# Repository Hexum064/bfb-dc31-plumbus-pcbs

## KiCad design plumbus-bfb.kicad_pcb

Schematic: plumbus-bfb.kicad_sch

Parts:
B1: mode; SW_PTS636_SM43J_SMTR_LFS
B2: key1; DTSM-21R-V-B
B3: key2; DTSM-21R-V-B
B4: key3; DTSM-21R-V-B
B5: key4; DTSM-21R-V-B
B6: reset; SW_PTS636_SM43J_SMTR_LFS
BT1: Battery; BatteryHolder_MPD_BC2AAPC_2xAA
C1, C2: 10uF; C_0603_1608Metric
C3, C6, C7, C8, C9, C11, C15, C16, C17, C18, C19, C20, C21, C22, C23, C24, C25, C26, C27, C28, C29, C30: .1uF; C_0603_1608Metric
C4: 0.1uF; C_0603_1608Metric
C5: 470uF; CP_EIA-7343-31_Kemet-D
C10: 100uF; CP_EIA-3528-12_Kemet-T
C12, C14: .474uF; C_0603_1608Metric
C13: .220uF; C_0603_1608Metric
D1, D2, D3: red; LED_0603_1608Metric
J1: Conn_01x04_Socket; PinHeader_1x04_P2.54mm_Horizontal
J2, J3: Conn_02x03_Odd_Even; PinSocket_2x03_P2.54mm_Vertical
L1: 2.2uH; L_1008_2520Metric
Q1: 2N7002; SOT-23
Q2: PZT2222A/MMBT2222A; SOT-23
R1, R12: 100; R_0603_1608Metric
R2, R6: 10k; R_0603_1608Metric
R3, R4, R5, R8, R9: 1k; R_0603_1608Metric
R7: 22k; R_0603_1608Metric
R10: 510; R_0603_1608Metric
R11: 47; R_0603_1608Metric
R13, R14: 4.7k; R_0603_1608Metric
RV1: 20k; TRIM_3352T-1-103LF
S1: SM150508-7
SW1: SW_SPST; MSS3VTR
U1: ATxmega16E5-M; QFN-32-1EP_5x5mm_P0.5mm_EP3.1x3.1mm
U2: TCA6416APWR; TSSOP-24_4.4x7.8mm_P0.65mm
U3: NCS2211DR2G/SC8002B; SOIC-8_3.9x4.9mm_P1.27mm
U4: TPS63001DRCR; VREG_V62_16624-01YE
U5, U6, U7, U8, U9, U10, U11, U12, U13, U14, U15, U16, U17, U18, U19, U20: KTH1601SL-ST3; SOT-23-3
U21, U22, U23, U24, U25, U26, U27, U28, U29, U30, U31, U32, U33, U34, U35, U36, U37, U38, U39, U40, U41, U42, U43, U44, U45, U46, U47, U48, U49, U50, U51, U52, U53, U54, U55, U56, U57, U58, U59, U60, U61, U62, U63, U64, U65, U66, U67, U68, U69, U70, U71, U72, U73, U74, U75, U76: ws2812b-1010

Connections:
+3.3V: C2.1, C3.1, C5.1, C6.1, C7.1, C8.1, C9.1, C10.1, C15.1, C16.1, C17.1, C18.1, C19.1, C20.1, C21.1, C22.1, C23.1, C24.1, C25.1, C26.1, C27.1, C28.1, C29.1, C30.1, J1.4, J2.1, J3.1, R2.1, R13.2, R14.1, U1.17 (VCC), U1.32 (AVCC), U2.2 (VCC1), U2.24 (VCCP), U3.6 (VCC), U4.1 (VOUT), U4.10 (FB), U5.1 (VCC), U6.1 (VCC), U7.1 (VCC), U8.1 (VCC), U9.1 (VCC), U10.1 (VCC), U11.1 (VCC), U12.1 (VCC), U13.1 (VCC), U14.1 (VCC), U15.1 (VCC), U16.1 (VCC), U17.1 (VCC), U18.1 (VCC), U19.1 (VCC), U20.1 (VCC), U21.2 (VDD), U22.2 (VDD), U23.2 (VDD), U24.2 (VDD), U25.2 (VDD), U26.2 (VDD), U27.2 (VDD), U28.2 (VDD), U29.2 (VDD), U30.2 (VDD), U31.2 (VDD), U32.2 (VDD), U33.2 (VDD), U34.2 (VDD), U35.2 (VDD), U36.2 (VDD), U37.2 (VDD), U38.2 (VDD), U39.2 (VDD), U40.2 (VDD), U41.2 (VDD), U42.2 (VDD), U43.2 (VDD), U44.2 (VDD), U45.2 (VDD), U46.2 (VDD), U47.2 (VDD), U48.2 (VDD), U49.2 (VDD), U50.2 (VDD), U51.2 (VDD), U52.2 (VDD), U53.2 (VDD), U54.2 (VDD), U55.2 (VDD), U56.2 (VDD), U57.2 (VDD), U58.2 (VDD), U59.2 (VDD), U60.2 (VDD), U61.2 (VDD), U62.2 (VDD), U63.2 (VDD), U64.2 (VDD), U65.2 (VDD), U66.2 (VDD), U67.2 (VDD), U68.2 (VDD), U69.2 (VDD), U70.2 (VDD), U71.2 (VDD), U72.2 (VDD), U73.2 (VDD), U74.2 (VDD), U75.2 (VDD), U76.2 (VDD)
GND: B1.2, B6.1, BT1.2 (-), C1.2, C2.2, C3.2, C4.2, C5.2, C7.2, C9.2, C10.2, C11.2, C13.2, J1.1, J2.2, J3.2, Q1.2 (S), R3.1, R4.1, R5.1, R6.1, U1.1 (GND), U1.18 (GND), U1.33 (GND), U3.1 (ENABLE), U3.7 (VEE), U4.3 (PGND), U4.9 (GND), U4.11 (THERMAL_PAD), U21.3 (GND), U22.3 (GND), U23.3 (GND), U24.3 (GND), U25.3 (GND), U26.3 (GND), U27.3 (GND), U28.3 (GND), U29.3 (GND), U30.3 (GND), U31.3 (GND), U32.3 (GND), U33.3 (GND), U34.3 (GND), U35.3 (GND), U36.3 (GND), U37.3 (GND), U38.3 (GND), U39.3 (GND), U40.3 (GND), U41.3 (GND), U42.3 (GND), U43.3 (GND), U44.3 (GND), U45.3 (GND), U46.3 (GND), U47.3 (GND), U48.3 (GND), U49.3 (GND), U50.3 (GND), U51.3 (GND), U52.3 (GND), U53.3 (GND), U54.3 (GND), U55.3 (GND), U56.3 (GND), U57.3 (GND), U58.3 (GND), U59.3 (GND), U60.3 (GND), U61.3 (GND), U62.3 (GND), U63.3 (GND), U64.3 (GND), U65.3 (GND), U66.3 (GND), U67.3 (GND), U68.3 (GND), U69.3 (GND), U70.3 (GND), U71.3 (GND), U72.3 (GND), U73.3 (GND), U74.3 (GND), U75.3 (GND), U76.3 (GND); also elsewhere on the board
unnamed: C12.1, R11.1, R12.1
unnamed: C12.2, R7.2
unnamed: C13.1, C14.2, R8.2
unnamed: C14.1, R9.1
unnamed: D1.2 (A), U1.23 (PD5)
unnamed: D1.1 (K), R5.2
unnamed: D2.2 (A), U1.22 (PD6)
unnamed: D2.1 (K), R4.2
unnamed: D3.2 (A), U1.21 (PD7)
unnamed: D3.1 (K), R3.2
unnamed: J1.2, U1.7 (PDI_DATA)
unnamed: B6.2, J1.3, U1.8 (~RESET/PDI_CLK)
unnamed: J2.5, J3.5, R9.2
unnamed: J2.6, U1.10 (PC6)
unnamed: J3.6, U1.11 (PC5)
unnamed: Q1.1 (G), R6.2, U1.9 (PC7)
unnamed: Q2.1 (B), R10.1
unnamed: Q2.2 (C), U1.12 (PC4)
unnamed: Q2.3 (E), R12.2
unnamed: R7.1, R8.1, RV1.1
unnamed: B1.1, U1.6 (AREF/PA0)
unnamed: R10.2, U1.4 (PA2)
unnamed 24: B2.1, B2.2, U1.2 (PA4); also elsewhere on the board
unnamed 25: B3.1, B3.2, U1.31 (PA5); also elsewhere on the board
unnamed 26: B4.1, B4.2, U1.30 (PA6); also elsewhere on the board
unnamed 27: B5.1, B5.2, U1.29 (PA7); also elsewhere on the board
unnamed: U1.28 (PD0/AREF), U21.4 (DI)
unnamed: R11.2, U1.24 (PD4)
unnamed: U2.4 (P00), U5.2 (VOUT)
unnamed: U2.5 (P01), U6.2 (VOUT)
unnamed: U2.6 (P02), U7.2 (VOUT)
unnamed: U2.7 (P03), U8.2 (VOUT)
unnamed: U2.8 (P04), U9.2 (VOUT)
unnamed: U2.20 (P17), U20.2 (VOUT)
unnamed: R2.2, U2.3 (~RESET)
unnamed: C11.1, U3.2 (BIAS), U3.3 (IN+)
unnamed: RV1.2, U3.4 (IN-)
unnamed: RV1.3, S1.1, U3.5 (OUT+)
unnamed: S1.2, U3.8 (OUT-)
unnamed: C4.1, R1.2, U4.6 (EN), U4.7 (PS/SYNC), U4.8 (VINA)
unnamed: L1.2, U4.4 (L1)
unnamed: L1.1, U4.2 (L2)
unnamed: U2.9 (P05), U10.2 (VOUT)
unnamed: U2.10 (P06), U11.2 (VOUT)
unnamed: U2.11 (P07), U12.2 (VOUT)
unnamed: U2.13 (P10), U13.2 (VOUT)
unnamed: U2.14 (P11), U14.2 (VOUT)
unnamed: U2.15 (P12), U15.2 (VOUT)
unnamed: U2.16 (P13), U16.2 (VOUT)
unnamed: U2.17 (P14), U17.2 (VOUT)
unnamed: U2.18 (P15), U18.2 (VOUT)
unnamed: U2.19 (P16), U19.2 (VOUT)
unnamed: U21.1 (DO), U22.4 (DI)
unnamed: U22.1 (DO), U23.4 (DI)
unnamed: U23.1 (DO), U24.4 (DI)
unnamed: U24.1 (DO), U25.4 (DI)
unnamed: U25.1 (DO), U26.4 (DI)
unnamed: U26.1 (DO), U27.4 (DI)
unnamed: U27.1 (DO), U28.4 (DI)
unnamed: U28.1 (DO), U29.4 (DI)
unnamed: U29.1 (DO), U30.4 (DI)
unnamed: U30.1 (DO), U31.4 (DI)
unnamed: U31.1 (DO), U32.4 (DI)
unnamed: U32.1 (DO), U33.4 (DI)
unnamed: U33.1 (DO), U34.4 (DI)
unnamed: U34.1 (DO), U35.4 (DI)
unnamed: U35.1 (DO), U36.4 (DI)
unnamed: U36.1 (DO), U37.4 (DI)
unnamed: U37.1 (DO), U38.4 (DI)
unnamed: U38.1 (DO), U39.4 (DI)
unnamed: U39.1 (DO), U40.4 (DI)
unnamed: U40.1 (DO), U41.4 (DI)
unnamed: U41.1 (DO), U42.4 (DI)
unnamed: U42.1 (DO), U43.4 (DI)
unnamed: U43.1 (DO), U44.4 (DI)
unnamed: U44.1 (DO), U45.4 (DI)
unnamed: U45.1 (DO), U46.4 (DI)
unnamed: U46.1 (DO), U47.4 (DI)
unnamed: U47.1 (DO), U48.4 (DI)
unnamed: U48.1 (DO), U49.4 (DI)
unnamed: U49.1 (DO), U50.4 (DI)
unnamed: U50.1 (DO), U51.4 (DI)
unnamed: U51.1 (DO), U52.4 (DI)
unnamed: U52.1 (DO), U53.4 (DI)
unnamed: U53.1 (DO), U54.4 (DI)
unnamed: U54.1 (DO), U55.4 (DI)
unnamed: U55.1 (DO), U56.4 (DI)
unnamed: U56.1 (DO), U57.4 (DI)
unnamed: U57.1 (DO), U58.4 (DI)
unnamed: U58.1 (DO), U59.4 (DI)
unnamed: U59.1 (DO), U60.4 (DI)
unnamed: U60.1 (DO), U61.4 (DI)
unnamed: U61.1 (DO), U62.4 (DI)
unnamed: U62.1 (DO), U63.4 (DI)
unnamed: U63.1 (DO), U64.4 (DI)
unnamed: U64.1 (DO), U65.4 (DI)
unnamed: U65.1 (DO), U66.4 (DI)
unnamed: U66.1 (DO), U67.4 (DI)
unnamed: U67.1 (DO), U68.4 (DI)
unnamed: U68.1 (DO), U69.4 (DI)
unnamed: U69.1 (DO), U70.4 (DI)
unnamed: U70.1 (DO), U71.4 (DI)
unnamed: U71.1 (DO), U72.4 (DI)
unnamed: U72.1 (DO), U73.4 (DI)
unnamed: U73.1 (DO), U74.4 (DI)
unnamed: U74.1 (DO), U75.4 (DI)
unnamed: U75.1 (DO), U76.4 (DI)
SCL: J2.4, J3.4, R13.1, U1.15 (PC1), U2.22 (SCL)
SDA: J2.3, J3.3, R14.2, U1.16 (PC0), U2.23 (SDA)
VEE: C6.2, C8.2, C15.2, C16.2, C17.2, C18.2, C19.2, C20.2, C21.2, C22.2, C23.2, C24.2, C25.2, C26.2, C27.2, C28.2, C29.2, C30.2, Q1.3 (D), U2.12 (GND), U2.21 (ADDR), U5.3 (GND), U6.3 (GND), U7.3 (GND), U8.3 (GND), U9.3 (GND), U10.3 (GND), U11.3 (GND), U12.3 (GND), U13.3 (GND), U14.3 (GND), U15.3 (GND), U16.3 (GND), U17.3 (GND), U18.3 (GND), U19.3 (GND), U20.3 (GND)

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
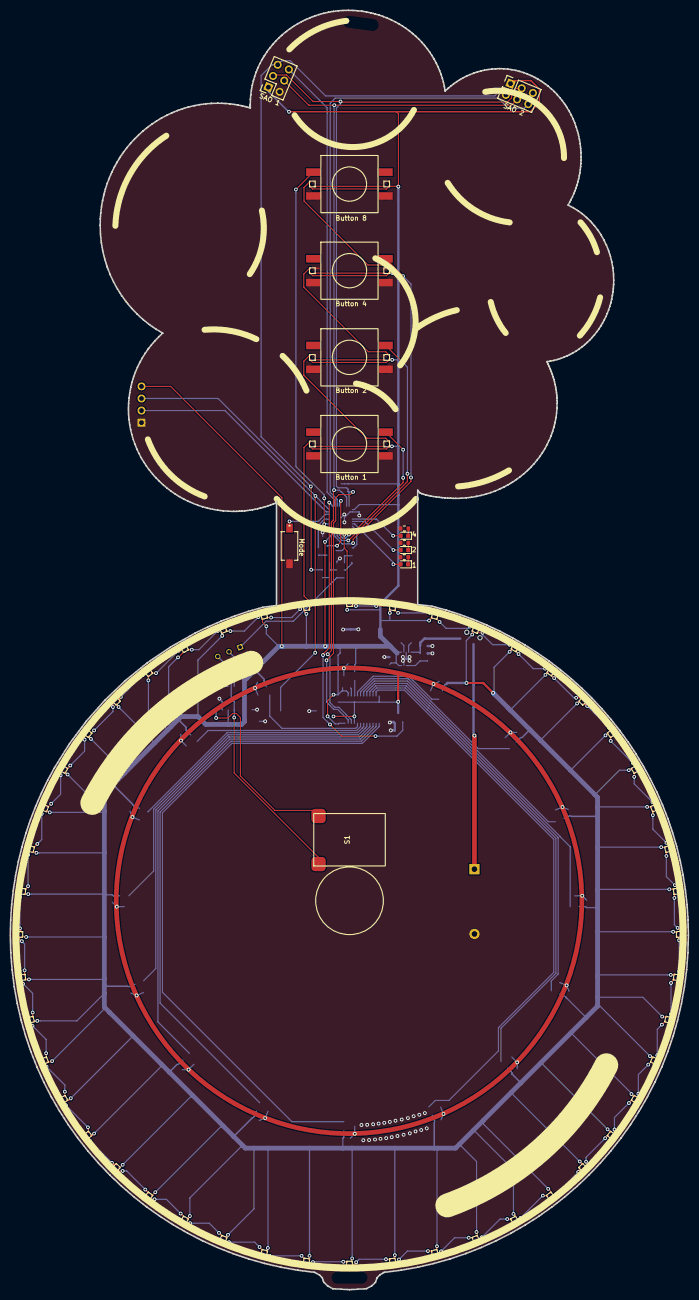
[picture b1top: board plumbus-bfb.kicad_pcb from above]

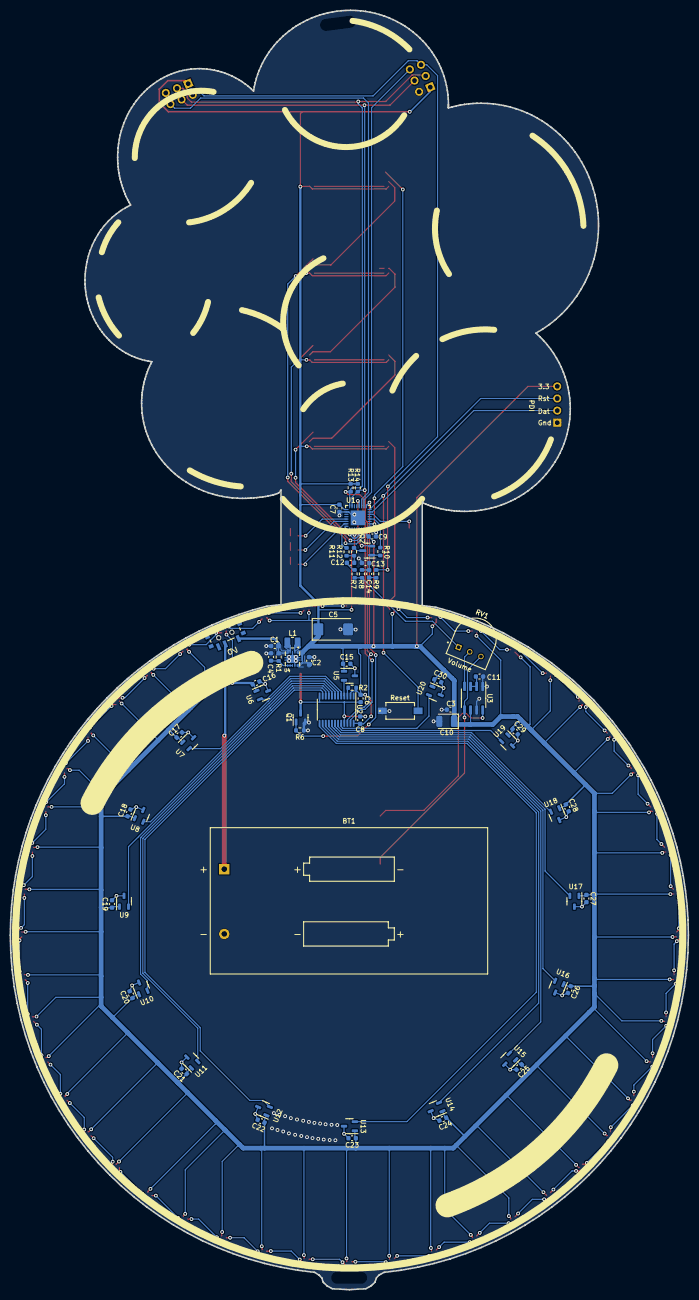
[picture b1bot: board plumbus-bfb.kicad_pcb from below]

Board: 2 copper layers, 142.3 x 268.4 mm, 139 parts (69 on the bottom side), 114 nets.

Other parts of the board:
key1: key1; DTSM-21R-V-B
key2: key2; DTSM-21R-V-B
key3: key3; DTSM-21R-V-B
key4: key4; DTSM-21R-V-B

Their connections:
GND: key1.3 (passive), key1.4 (passive), key2.3 (passive), key2.4 (passive), key3.3 (passive), key3.4 (passive), key4.3 (passive), key4.4 (passive); also elsewhere on the board
unnamed 24: key1.1, key1.2; also elsewhere on the board
unnamed 25: key2.1, key2.2; also elsewhere on the board
unnamed 26: key3.1, key3.2; also elsewhere on the board
unnamed 27: key4.1, key4.2; also elsewhere on the board

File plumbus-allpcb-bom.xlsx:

|  |  | floob-dome-switches BOM
Item # | *Ref Des | *Qty | Manufacturer | *Mfg Part # | Description / Value | *Package | Type | Your Instructions / Notes
1 | B1 | 1 | LCSC | C2800965 | TS-1101-C-W:SW_PTS636_SM43J_SMTR_LFS | TS-1101-C-W:SW_PTS636_SM43J_SMTR_LFS | mode
2 | B6 | 1 | LCSC | C2800965 | TS-1101-C-W:SW_PTS636_SM43J_SMTR_LFS | TS-1101-C-W:SW_PTS636_SM43J_SMTR_LFS | reset
3 | C1, C2 | 2 | LCSC | C19702 | Capacitor_SMD:C_0603_1608Metric | Capacitor_SMD:C_0603_1608Metric | 10uF
4 | C3, C6, C7, C8, C9, C11, C15, C16, C17, C18, C19, C20, C21, C22, C23, C24, C25,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 | 22 | LCSC | C15849 | Capacitor_SMD:C_0603_1608Metric | Capacitor_SMD:C_0603_1608Metric | .1uF
5 | C4 | 1 | LCSC | C14663 | Capacitor_SMD:C_0603_1608Metric | Capacitor_SMD:C_0603_1608Metric | 0.1uF
6 | C5 | 1 | LCSC | C123270 | Capacitor_Tantalum_SMD:CP_EIA-7343-31_Kemet-D | Capacitor_Tantalum_SMD:CP_EIA-7343-31_Kemet-D | 470uF
7 | C10 | 1 | LCSC | C140373 | Capacitor_Tantalum_SMD:CP_EIA-3528-12_Kemet-T | Capacitor_Tantalum_SMD:CP_EIA-3528-12_Kemet-T | 100uF
8 | C12, C14 | 2 | LCSC | C1623 | Capacitor_SMD:C_0603_1608Metric | Capacitor_SMD:C_0603_1608Metric | .474uF
9 | C13 | 1 | LCSC | C5189829 | Capacitor_SMD:C_0603_1608Metric | Capacitor_SMD:C_0603_1608Metric | .220uF
10 | D1, D2, D3 | 3 | LCSC | C965799 | LED_SMD:LED_0603_1608Metric | LED_SMD:LED_0603_1608Metric | red
11 | J2, J3 | 2 | LCSC | C2935983 | Connector_PinSocket_2.54mm:PinSocket_2x03_P2.54mm_Vertical | Connector_PinSocket_2.54mm:PinSocket_2x03_P2.54mm_Vertical | Conn_02x03_Odd_Even
12 | L1 | 1 | LCSC | C488330 | Inductor_SMD:L_1008_2520Metric | Inductor_SMD:L_1008_2520Metric | 2.2uH
13 | Q1 | 1 | LCSC | C8545 | Package_TO_SOT_SMD:SOT-23 | Package_TO_SOT_SMD:SOT-23 | 2N7002
14 | Q2 | 1 | LCSC | C545537 | Package_TO_SOT_SMD:SOT-23 | Package_TO_SOT_SMD:SOT-23 | PZT2222A/MMBT2222A
15 | R1, R12 | 2 | LCSC | C22775 | Resistor_SMD:R_0603_1608Metric | Resistor_SMD:R_0603_1608Metric | 100
16 | R2, R6 | 2 | LCSC | C25804 | Resistor_SMD:R_0603_1608Metric | Resistor_SMD:R_0603_1608Metric | 10k
17 | R3, R4, R5, R8, R9 | 5 | LCSC | C21190 | Resistor_SMD:R_0603_1608Metric | Resistor_SMD:R_0603_1608Metric | 1k
18 | R7 | 1 | LCSC | C31850 | Resistor_SMD:R_0603_1608Metric | Resistor_SMD:R_0603_1608Metric | 22k
19 | R10 | 1 | LCSC | C23193 | Resistor_SMD:R_0603_1608Metric | Resistor_SMD:R_0603_1608Metric | 510
20 | R11 | 1 | LCSC | C23182 | Resistor_SMD:R_0603_1608Metric | Resistor_SMD:R_0603_1608Metric | 47
21 | R13, R14 | 2 | LCSC | C23162 | Resistor_SMD:R_0603_1608Metric | Resistor_SMD:R_0603_1608Metric | 4.7k
22 | SW1 | 1 | LCSC | C730329 | MSS3-V-T/TA-3524A-A1-W:MSS3VTR | MSS3-V-T/TA-3524A-A1-W:MSS3VTR | SW_SPST
24 | U2 | 1 | LCSC | C130203 | Package_SO:TSSOP-24_4.4x7.8mm_P0.65mm | Package_SO:TSSOP-24_4.4x7.8mm_P0.65mm | TCA6416APWR
25 | U3 | 1 | LCSC | C82124 | Package_SO:SOIC-8_3.9x4.9mm_P1.27mm | Package_SO:SOIC-8_3.9x4.9mm_P1.27mm | NCS2211DR2G/SC8002B
26 | U4 | 1 | LCSC | C28060 | TPS63001DRCR:VREG_V62_16624-01YE | TPS63001DRCR:VREG_V62_16624-01YE | TPS63001DRCR
27 | U5, U6, U7, U8, U9, U10, U11, U12, U13, U14, U15, U16, U17, U18, U19, U20 | 16 | LCSC | C516265 | Package_TO_SOT_SMD:SOT-23-3 | Package_TO_SOT_SMD:SOT-23-3 | KTH1601SL-ST3
28 | U21, U22, U23, U24, U25, U26, U27, U28, U29, U30, U31, U32, U33, U34, U35, U36,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 | 56 | LCSC | C5349953 | ws2812b-1010:ws2812b-1010 | ws2812b-1010:ws2812b-1010 | 1mx1m

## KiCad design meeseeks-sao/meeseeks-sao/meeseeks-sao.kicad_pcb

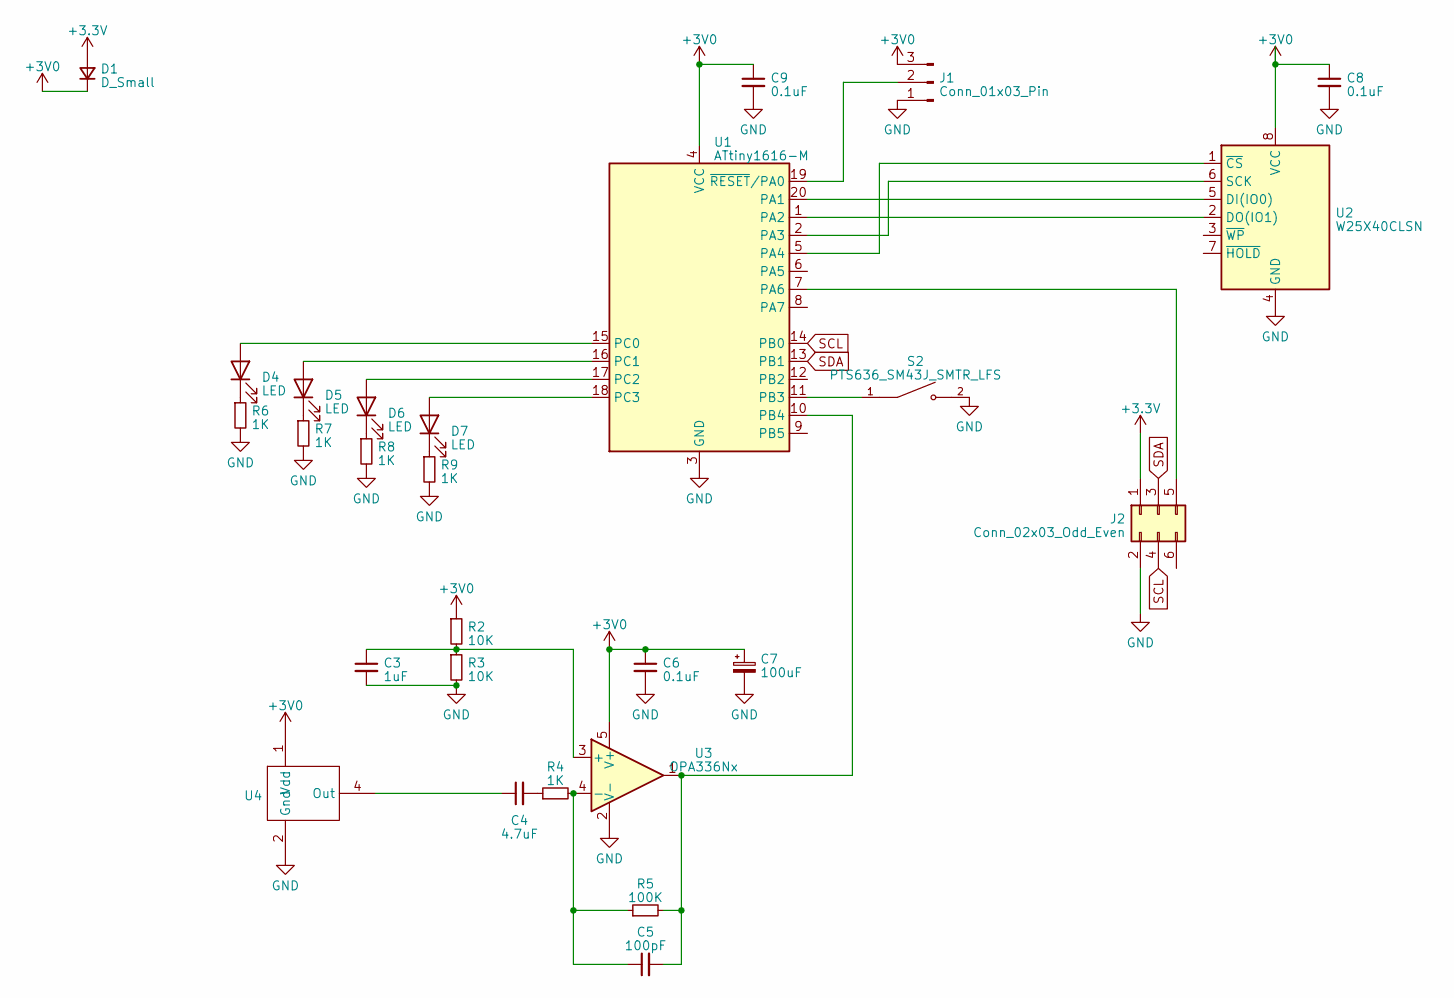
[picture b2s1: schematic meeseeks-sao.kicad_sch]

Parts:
C3: 1uF; C_0603_1608Metric
C4: 4.7uF; C_0603_1608Metric
C5: 100pF; C_0603_1608Metric
C6, C8, C9: 0.1uF; C_0603_1608Metric
C7: 100uF; CP_EIA-3528-12_Kemet-T
D1: D_Small; D_0603_1608Metric
D4, D5, D6, D7: LED; LED_0603_1608Metric
J1: Conn_01x03_Pin; SolderJumper-3_P1.3mm_Open_RoundedPad1.0x1.5mm
J2: Conn_02x03_Odd_Even; PinHeader_2x03_P2.54mm_Vertical
R2, R3: 10K; R_0603_1608Metric
R4, R6, R7, R8, R9: 1K; R_0603_1608Metric
R5: 100K; R_0603_1608Metric
S2: PTS636_SM43J_SMTR_LFS; SW_PTS636_SM43J_SMTR_LFS; PARTREV 27 mar 19
U1: ATtiny1616-M; VQFN-20-1EP_3x3mm_P0.4mm_EP1.7x1.7mm
U2: W25X40CLSN; SOIC-8_3.9x4.9mm_P1.27mm
U3: OPA336Nx; SOT-23-5
U4: NSM2402AT

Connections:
+3.3V: D1.2 (A), J2.1; also elsewhere on the board
+3V0: C6.1, C7.1, C8.1, C9.1, D1.1 (K), J1.3, R2.1, U1.4 (VCC), U2.8 (VCC), U3.5 (V+), U4.1 (Vdd)
GND: C3.2, C6.2, C7.2, C8.2, C9.2, J1.1, J2.2, R3.2, R6.2, R7.2, R8.2, R9.2, S2.2, U1.3 (GND), U1.21 (GND), U2.4 (GND), U3.2 (V-), U4.2 (Gnd), U4.3 (Gnd); also elsewhere on the board
unnamed: C4.2, R4.1
unnamed: D4.2 (A), U1.15 (PC0)
unnamed: D4.1 (K), R6.1
unnamed: D5.2 (A), U1.16 (PC1)
unnamed: D5.1 (K), R7.1
unnamed: D6.2 (A), U1.17 (PC2)
unnamed: D6.1 (K), R8.1
unnamed: D7.2 (A), U1.18 (PC3)
unnamed: D7.1 (K), R9.1
unnamed: J1.2, U1.19 (~RESET/PA0)
unnamed 13: J2.5, U1.7 (PA6); also elsewhere on the board
unnamed: U1.20 (PA1), U2.5 (DI(IO0))
unnamed: U1.1 (PA2), U2.2 (DO(IO1))
unnamed: U1.2 (PA3), U2.6 (SCK)
unnamed: U1.5 (PA4), U2.1 (~CS)
unnamed: S2.1, U1.11 (PB3)
unnamed: C5.2, R5.2, U1.10 (PB4), U3.1
unnamed: C3.1, R2.2, R3.1, U3.3 (+)
unnamed: C5.1, R4.2, R5.1, U3.4 (-)
unnamed: C4.1, U4.4 (Out)
SCL: J2.4, U1.14 (PB0); also elsewhere on the board
SDA: J2.3, U1.13 (PB1); also elsewhere on the board

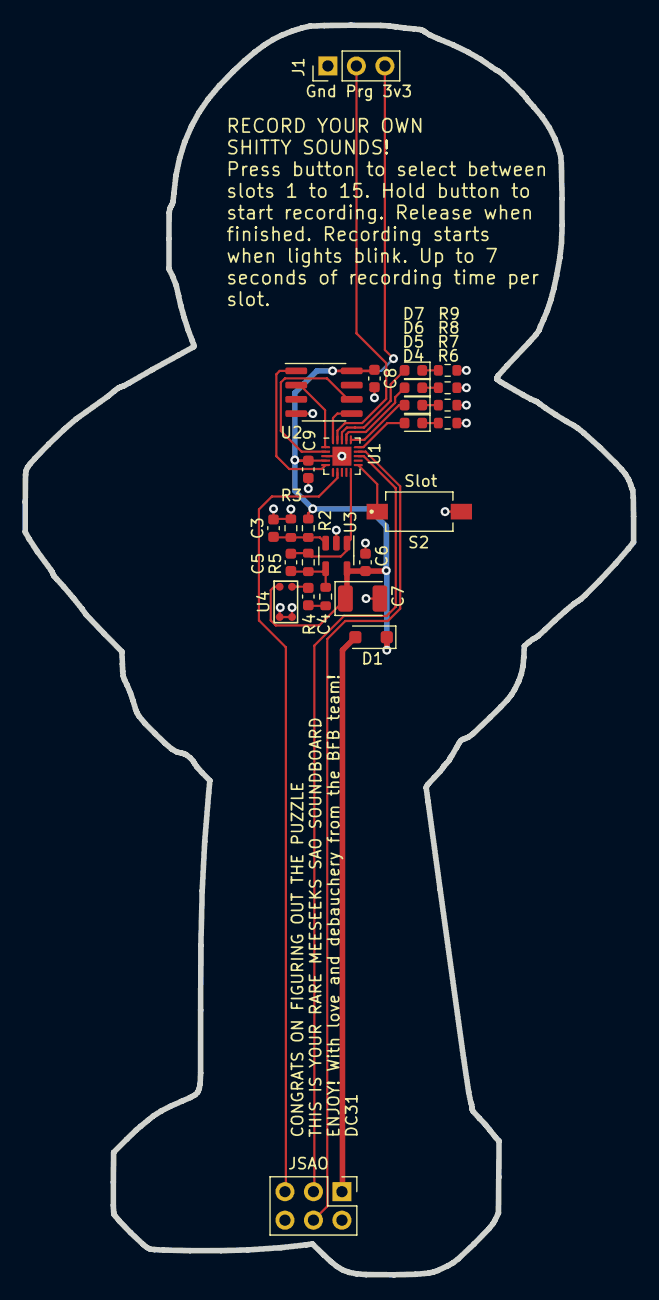
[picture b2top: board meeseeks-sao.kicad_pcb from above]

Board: 2 copper layers, 54.3 x 111.4 mm, 27 parts (0 on the bottom side), 25 nets.

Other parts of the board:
JSAO: Conn_02x03_Odd_Even; PinHeader_2x03_P2.54mm_Vertical

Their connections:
+3.3V: JSAO.1; also elsewhere on the board
GND: JSAO.2; also elsewhere on the board
unnamed 13: JSAO.5; also elsewhere on the board
SCL: JSAO.4; also elsewhere on the board
SDA: JSAO.3; also elsewhere on the board

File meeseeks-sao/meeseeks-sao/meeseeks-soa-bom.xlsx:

Comment | Reference(s) | Footprint | JLCPCB Part #（optional）
1uF | C3 | Capacitor_SMD:C_0603_1608Metric
4.7uF | C4 | Capacitor_SMD:C_0603_1608Metric
100pF | C5 | Capacitor_SMD:C_0603_1608Metric
0.1uF | C6, C8, C9 | Capacitor_SMD:C_0603_1608Metric
100uF | C7 | Capacitor_Tantalum_SMD:CP_EIA-3528-12_Kemet-T | C129567
D_Small | D1 | Diode_SMD:SOD-123FL | C2902912
LED | D4, D5, D6, D7 | LED_SMD:LED_0603_1608Metric | C965799
Conn_02x03_Odd_Even | J2 | Connector_PinHeader_2.54mm:PinHeader_2x03_P2.54mm_Vertical | C376086
10K | R2, R3 | Resistor_SMD:R_0603_1608Metric
1K | R4, R6, R7, R8, R9 | Resistor_SMD:R_0603_1608Metric
100K | R5 | Resistor_SMD:R_0603_1608Metric
PTS636_SM43J_SMTR_LFS | S2 | TS-1101-C-W:SW_PTS636_SM43J_SMTR_LFS | C318938
ATtiny1616-M | U1 | Package_DFN_QFN:VQFN-20-1EP_3x3mm_P0.4mm_EP1.7x1.7mm | C507118
W25Q16JVSNIQ | U2 | Package_SO:SOIC-8_3.9x4.9mm_P1.27mm | C2456211
OPA336Nx | U3 | Package_TO_SOT_SMD:SOT-23-5 | C3018990
~ | U4 | NSM2402AT-LL:NSM2402AT | C140704

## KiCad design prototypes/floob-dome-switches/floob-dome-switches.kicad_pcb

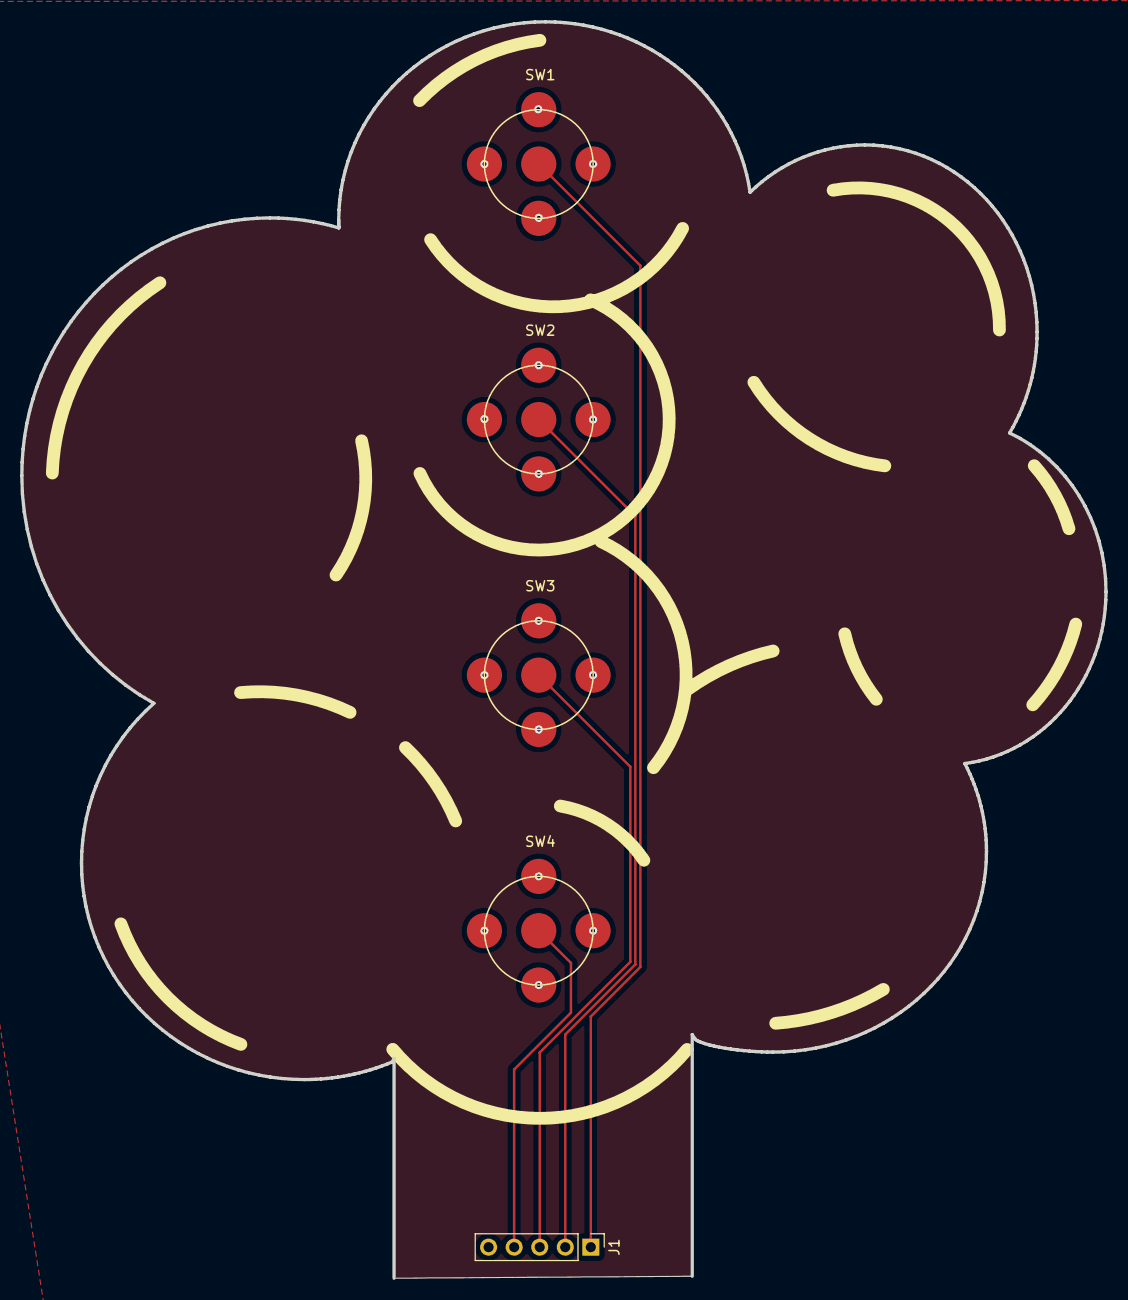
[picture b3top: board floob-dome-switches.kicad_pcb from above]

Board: 2 copper layers, 107.8 x 124.9 mm, 5 parts (0 on the bottom side), 5 nets.

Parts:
J1: Conn_01x05_Pin; PinHeader_1x05_P2.54mm_Vertical
SW1, SW2, SW3, SW4: SW_Push; 5173_cross_dome

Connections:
unnamed: J1.1, SW1.1
unnamed: J1.2, SW2.1
unnamed: J1.3, SW3.1
unnamed: J1.4, SW4.1
unnamed: J1.5, SW1.2, SW2.2, SW3.2, SW4.2

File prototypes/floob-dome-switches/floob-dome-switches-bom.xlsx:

|  |  | floob-dome-switches BOM
Item # | *Ref Des | *Qty | Manufacturer | *Mfg Part # | Description / Value | *Package | Type | Your Instructions / Notes
1 | SW1,SW2,SW3,SW4 | 4 | Keystone Electronics | 5174TR | Keybad Dome Switch | Leadless | SMD | These do not get soldered onto the PCB. They are taped in place. Please see dat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

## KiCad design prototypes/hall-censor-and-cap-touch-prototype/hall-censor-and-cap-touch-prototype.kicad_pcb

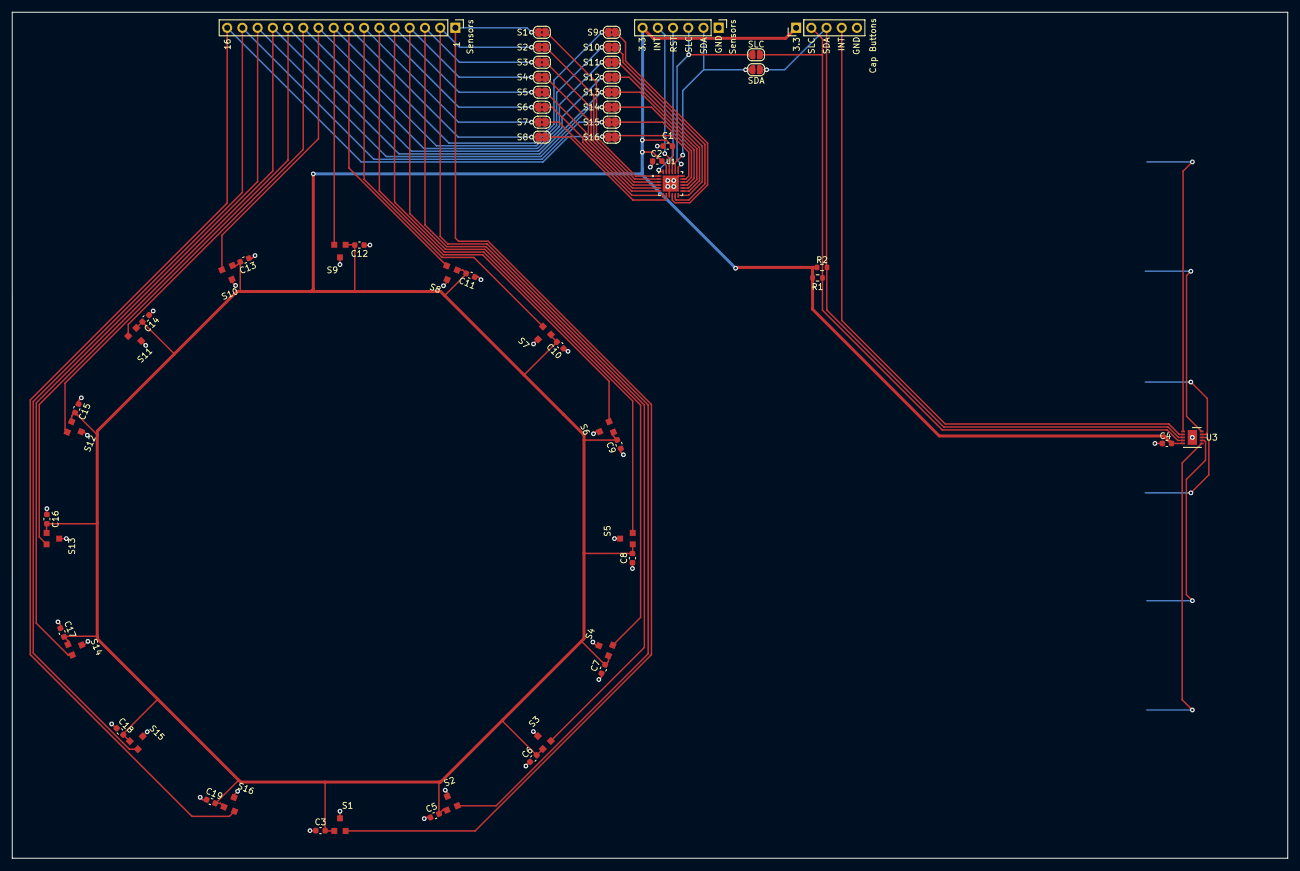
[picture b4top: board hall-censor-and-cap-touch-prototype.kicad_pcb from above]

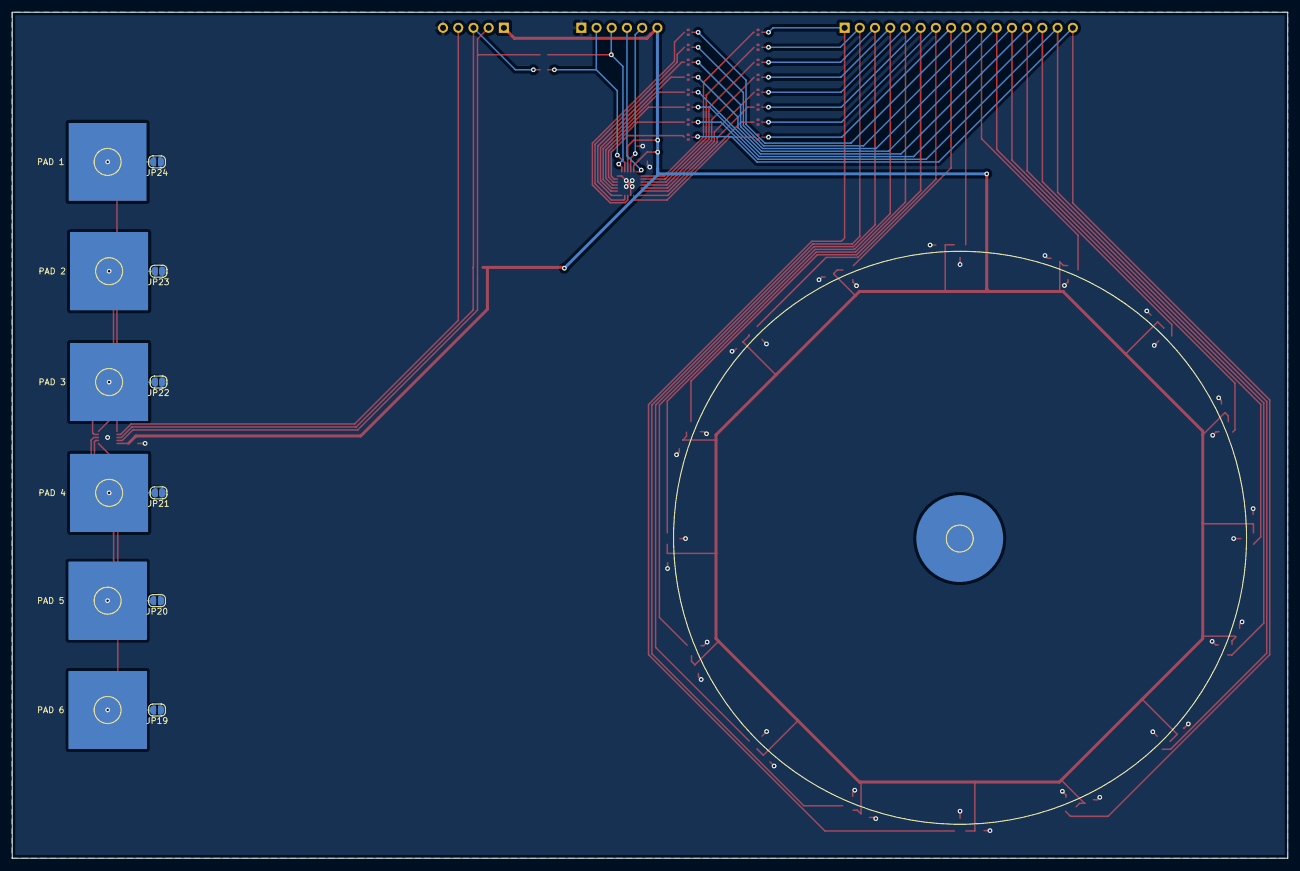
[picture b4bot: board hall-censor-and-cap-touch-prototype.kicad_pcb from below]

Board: 2 copper layers, 212.9 x 141.2 mm, 72 parts (12 on the bottom side), 47 nets.

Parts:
C1, C2, C4: 0.1uF; C_0603_1608Metric
C3, C5, C6, C7, C8, C9, C10, C11, C12, C13, C14, C15, C16, C17, C18, C19: 0.1 uF; C_0603_1608Metric
Cap Buttons: Conn_01x05_Female; PinHeader_1x05_P2.54mm_Vertical
JP19, JP20, JP21, JP22, JP23, JP24: SolderJumper_2_Open; SolderJumper-2_P1.3mm_Open_RoundedPad1.0x1.5mm
PAD 1, PAD 2, PAD 3, PAD 4, PAD 5, PAD 6: TestPoint_Pad_D4.0mm
R1, R2: 10K; R_0603_1608Metric
S1, S2, S3, S4, S5#2, S6, S7#2, S8#2, S9, S10, S11#2, S12#2, S13#2, S14, S15, S16: SolderJumper_2_Bridged; SolderJumper-2_P1.3mm_Bridged2Bar_RoundedPad1.0x1.5mm
S1#2, S2#2, S3#2, S4#2, S5, S6#2, S7, S8, S9#2, S10#2, S11, S12, S13, S14#2, S15#2, S16#2: AH3582-SA-7; SOT-23-AH3582-SA-7
SDA: SolderJumper_2_Open; SolderJumper-2_P1.3mm_Open_RoundedPad1.0x1.5mm
SLC: SolderJumper_2_Open; SolderJumper-2_P1.3mm_Open_RoundedPad1.0x1.5mm
Sensors: Conn_01x16_Female; PinHeader_1x16_P2.54mm_Vertical
Sensors#2: Conn_01x06_Female; PinHeader_1x06_P2.54mm_Vertical
U1: KTS1622EUAA-TR; QFN50P400X400X80-25N
U3: CAP1206-x-AIA; DFN-10-1EP_3x3mm_P0.5mm_EP1.55x2.48mm

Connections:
+3V3: C1.1, C2.1, C3.2, C4.1, C5.2, C6.2, C7.2, C8.2, C9.2, C10.2, C11.2, C12.2, C13.2, C14.2, C15.2, C16.2, C17.2, C18.2, C19.2, Cap Buttons.1, R1.1, R2.2, S1#2.1 (VCC), S2#2.1 (VCC), S3#2.1 (VCC), S4#2.1 (VCC), S5.1 (VCC), S6#2.1 (VCC), S7.1 (VCC), S8.1 (VCC), S9#2.1 (VCC), S10#2.1 (VCC), S11.1 (VCC), S12.1 (VCC), S13.1 (VCC), S14#2.1 (VCC), S15#2.1 (VCC), S16#2.1 (VCC), Sensors#2.6, U1.21 (VDD_P), U1.23 (VDD_I2C), U3.5 (VDD)
GND: C1.2, C2.2, C3.1, C4.2, C5.1, C6.1, C7.1, C8.1, C9.1, C10.1, C11.1, C12.1, C13.1, C14.1, C15.1, C16.1, C17.1, C18.1, C19.1, Cap Buttons.5, JP19.1 (A), JP20.1 (A), JP21.1 (A), JP22.1 (A), JP23.1 (A), JP24.1 (A), S1#2.3 (GND), S2#2.3 (GND), S3#2.3 (GND), S4#2.3 (GND), S5.3 (GND), S6#2.3 (GND), S7.3 (GND), S8.3 (GND), S9#2.3 (GND), S10#2.3 (GND), S11.3 (GND), S12.3 (GND), S13.3 (GND), S14#2.3 (GND), S15#2.3 (GND), S16#2.3 (GND), Sensors#2.1, U1.9 (VSS), U1.18 (ADDR), U1.25 (MC), U3.11 (GND)
unnamed: JP23.2 (B), U3.10 (CS2)
unnamed: JP22.2 (B), U3.9 (CS3)
unnamed: JP21.2 (B), U3.8 (CS4)
unnamed: JP20.2 (B), U3.7 (CS5)
unnamed: JP19.2 (B), U3.6 (CS6)
unnamed: S1.1 (A), S1#2.2 (OUT), Sensors.1
unnamed: S2.1 (A), S2#2.2 (OUT), Sensors.2
unnamed: S3.1 (A), S3#2.2 (OUT), Sensors.3
unnamed: S4.1 (A), S4#2.2 (OUT), Sensors.4
unnamed: S5.2 (OUT), S5#2.1 (A), Sensors.5
unnamed: S6.1 (A), S6#2.2 (OUT), Sensors.6
unnamed: S7.2 (OUT), S7#2.1 (A), Sensors.7
unnamed: S8.2 (OUT), S8#2.1 (A), Sensors.8
unnamed: S9.2 (B), S9#2.2 (OUT), Sensors.9
unnamed: S10.2 (B), S10#2.2 (OUT), Sensors.10
unnamed: S11.2 (OUT), S11#2.2 (B), Sensors.11
unnamed: S12.2 (OUT), S12#2.2 (B), Sensors.12
unnamed: S13.2 (OUT), S13#2.2 (B), Sensors.13
unnamed: S14.2 (B), S14#2.2 (OUT), Sensors.14
unnamed: S15.2 (B), S15#2.2 (OUT), Sensors.15
unnamed: S16.2 (B), S16#2.2 (OUT), Sensors.16
unnamed: SDA.2 (B), Sensors#2.2, U1.20 (SDA)
unnamed: SLC.2 (B), Sensors#2.3, U1.19 (SCL)
unnamed: Sensors#2.4, U1.24 (~RESET)
unnamed: Sensors#2.5, U1.22 (~INT)
unnamed: Cap Buttons.2, R1.2, SLC.1 (A), U3.4 (SMCLK)
unnamed: Cap Buttons.3, R2.1, SDA.1 (A), U3.3 (SMDATA)
unnamed: Cap Buttons.4, U3.2 (ALERT#)
unnamed: S1.2 (B), U1.1 (P0_0)
unnamed: S9.1 (A), U1.10 (P1_0)
unnamed: S2.2 (B), U1.2 (P0_1)
unnamed: S10.1 (A), U1.11 (P1_1)
unnamed: S3.2 (B), U1.3 (P0_2)
unnamed: S11#2.1 (A), U1.12 (P1_2)
unnamed: S4.2 (B), U1.4 (P0_3)
unnamed: S12#2.1 (A), U1.13 (P1_3)
unnamed: S5#2.2 (B), U1.5 (P0_4)
unnamed: S13#2.1 (A), U1.14 (P1_4)
unnamed: S6.2 (B), U1.6 (P0_5)
unnamed: S14.1 (A), U1.15 (P1_5)
unnamed: S7#2.2 (B), U1.7 (P0_6)
unnamed: S15.1 (A), U1.16 (P1_6)
unnamed: S8#2.2 (B), U1.8 (P0_7)
unnamed: S16.1 (A), U1.17 (P1_7)
unnamed: JP24.2 (B), U3.1 (CS1)

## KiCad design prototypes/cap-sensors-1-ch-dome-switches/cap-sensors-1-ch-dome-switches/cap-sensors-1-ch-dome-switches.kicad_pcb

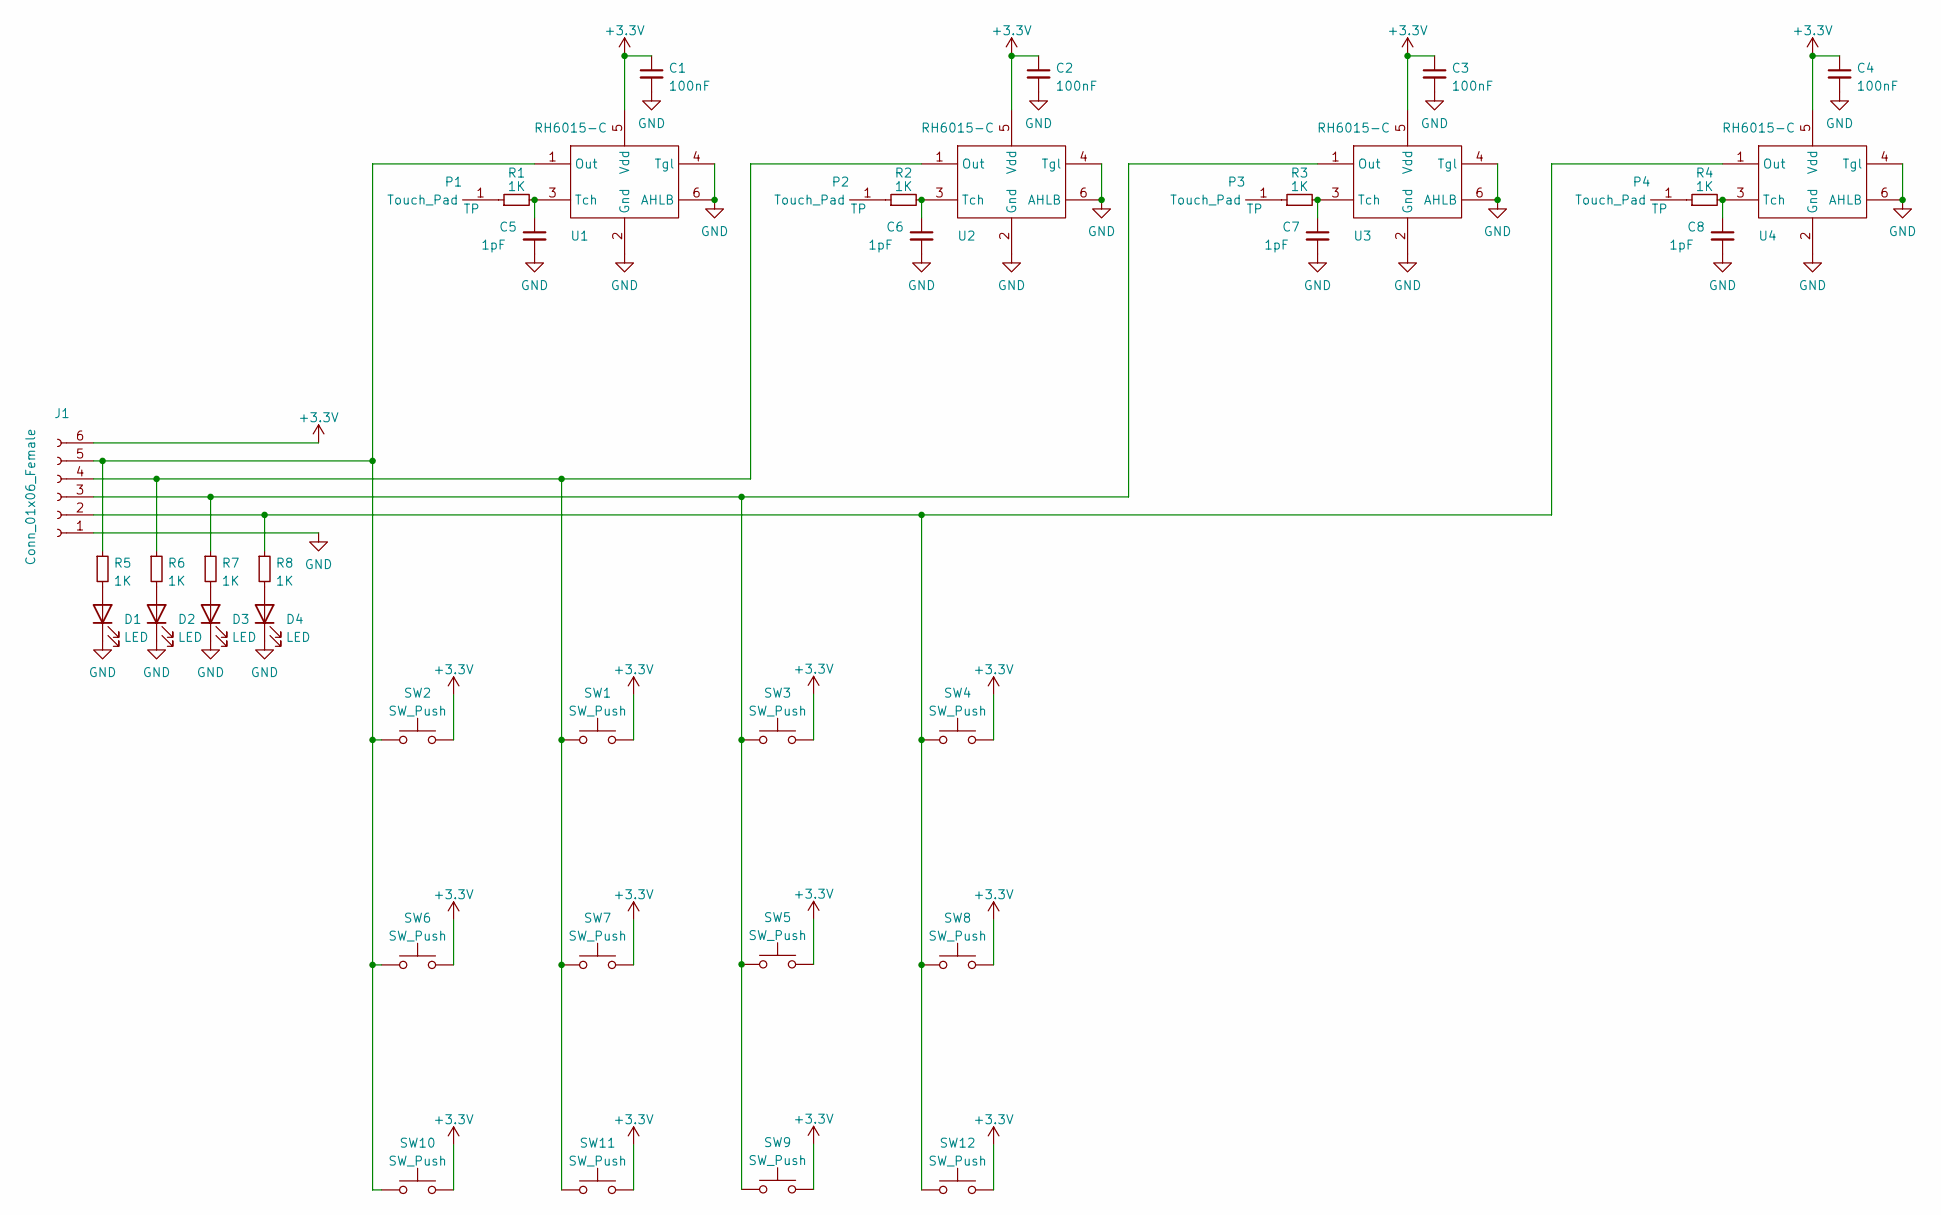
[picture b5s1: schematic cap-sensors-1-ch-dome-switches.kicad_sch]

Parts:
C1, C2, C3, C4: 100nF; C_0603_1608Metric
C5, C6, C7, C8: 1pF; C_0603_1608Metric
D1, D2, D3, D4: LED; LED_0603_1608Metric
J1: Conn_01x06_Female; PinHeader_1x06_P2.54mm_Vertical
P1, P2, P3, P4: TP; touch_pad
R1, R2, R3, R4, R5, R6, R7, R8: 1K; R_0603_1608Metric
SW1, SW2, SW3, SW4: SW_Push; EVQPLDA15
SW5, SW6, SW7, SW8: SW_Push; GT-TC170B-H0078-L10
SW9, SW10, SW11, SW12: SW_Push; TS5208A
U1, U2, U3, U4: RH6015-C

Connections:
+3V3: C1.1, C2.1, C3.1, C4.1, J1.6, SW1.B, SW2.B, SW3.B, SW4.B, SW5.2, SW6.2, SW7.2, SW8.2, SW9.2, SW10.2, SW11.2, SW12.2, U1.5 (Vdd), U2.5 (Vdd), U3.5 (Vdd), U4.5 (Vdd)
GND: C1.2, C2.2, C3.2, C4.2, C5.2, C6.2, C7.2, C8.2, D1.1 (K), D2.1 (K), D3.1 (K), D4.1 (K), J1.1, U1.2 (Gnd), U1.4 (Tgl), U1.6 (AHLB), U2.2 (Gnd), U2.4 (Tgl), U2.6 (AHLB), U3.2 (Gnd), U3.4 (Tgl), U3.6 (AHLB), U4.2 (Gnd), U4.4 (Tgl), U4.6 (AHLB)
unnamed: C5.1, R1.2, U1.3 (Tch)
unnamed: C6.1, R2.2, U2.3 (Tch)
unnamed: C7.1, R3.2, U3.3 (Tch)
unnamed: C8.1, R4.2, U4.3 (Tch)
unnamed: D1.2 (A), R5.2
unnamed: D2.2 (A), R6.2
unnamed: D3.2 (A), R7.2
unnamed: D4.2 (A), R8.2
unnamed: J1.2, R8.1, SW4.A, SW8.1, SW12.1, U4.1 (Out)
unnamed: J1.3, R7.1, SW3.A, SW5.1, SW9.1, U3.1 (Out)
unnamed: J1.4, R6.1, SW1.A, SW7.1, SW11.1, U2.1 (Out)
unnamed: J1.5, R5.1, SW2.A, SW6.1, SW10.1, U1.1 (Out)
unnamed 14: P1.1, R1.1; also elsewhere on the board
unnamed 15: P2.1, R2.1; also elsewhere on the board
unnamed 16: P3.1, R3.1; also elsewhere on the board
unnamed 17: P4.1, R4.1; also elsewhere on the board
